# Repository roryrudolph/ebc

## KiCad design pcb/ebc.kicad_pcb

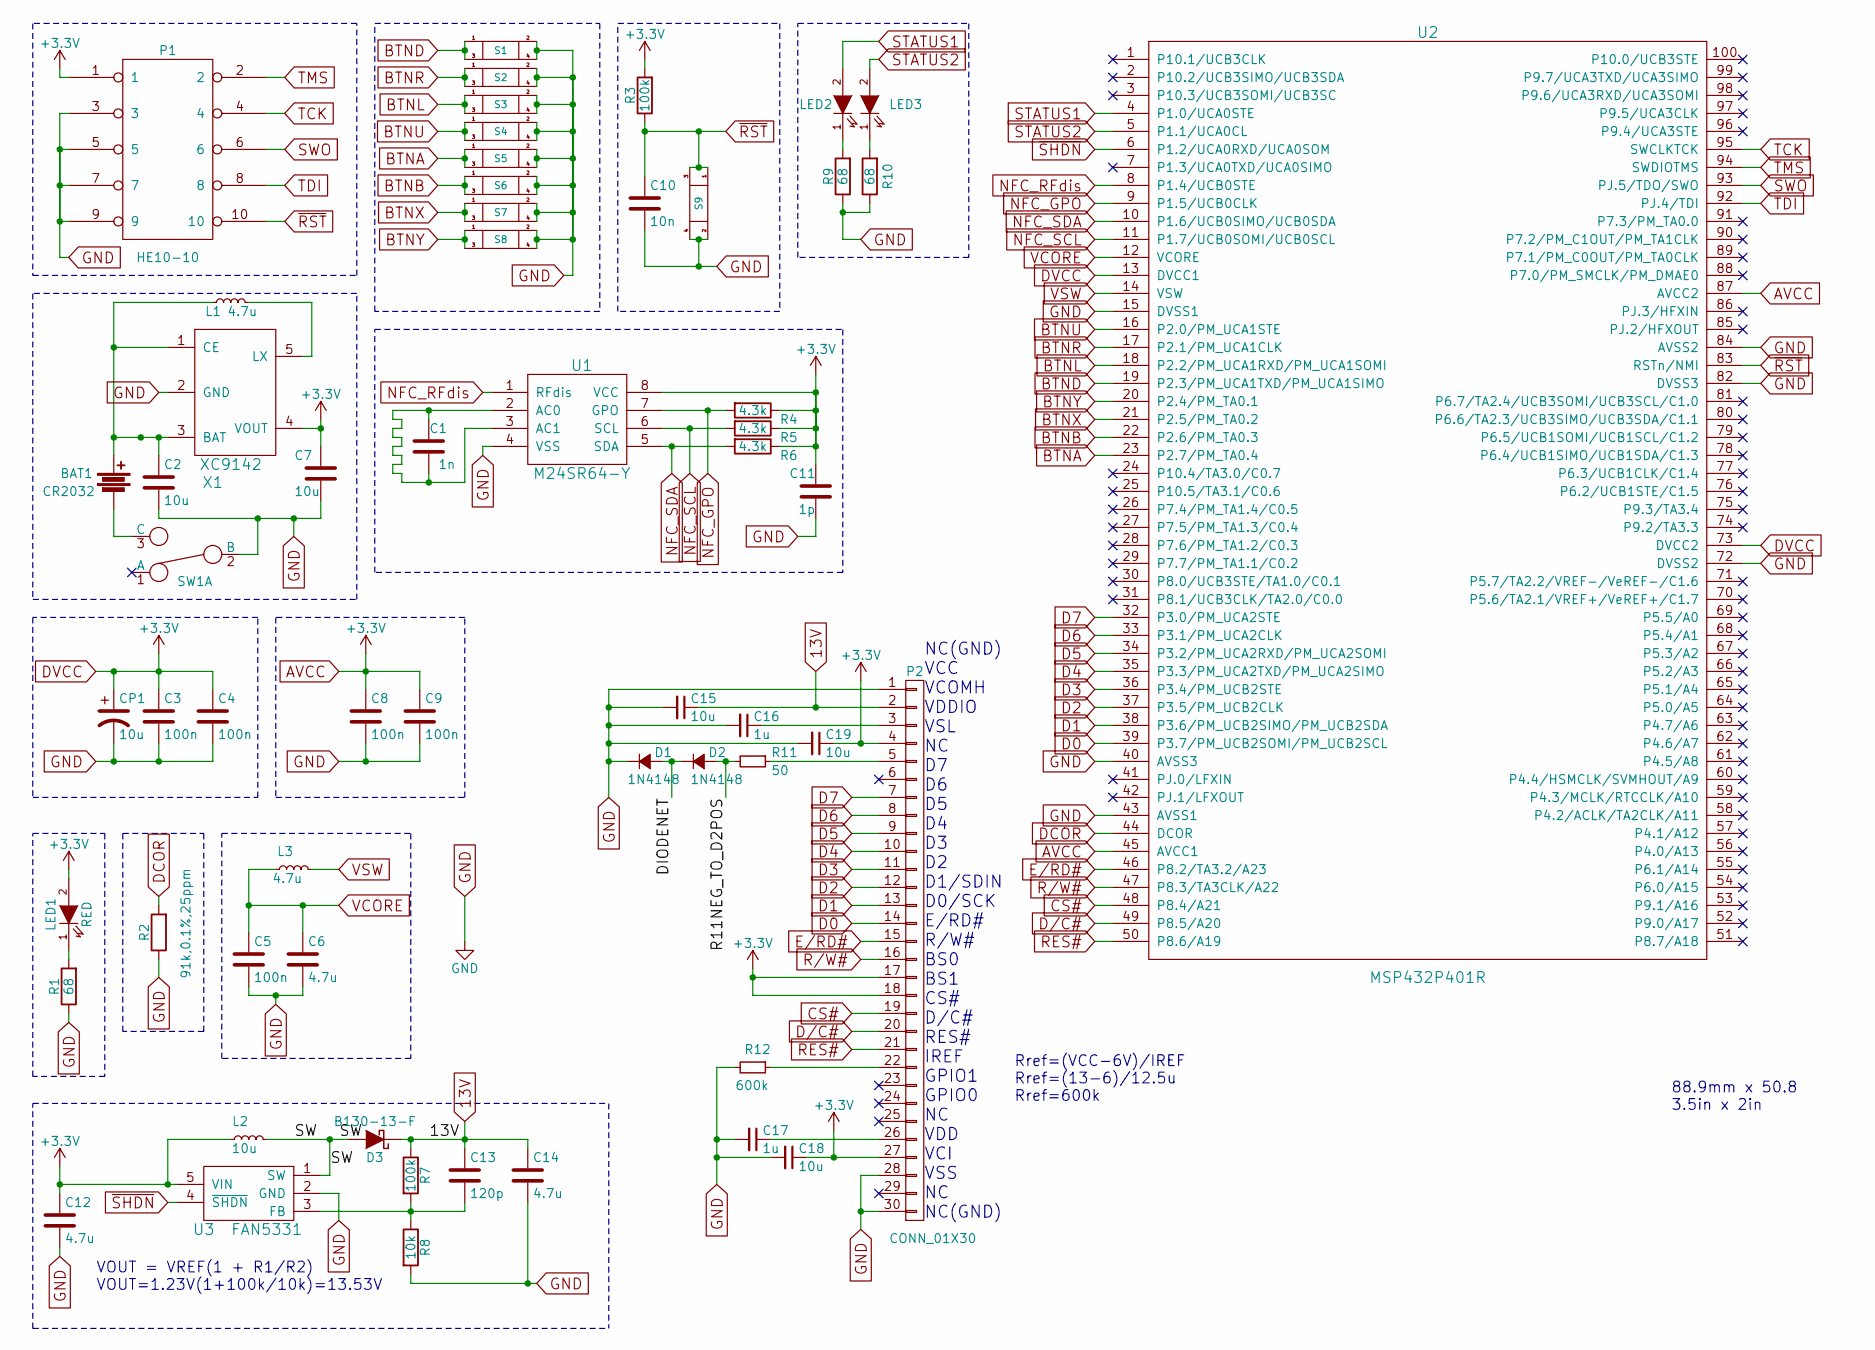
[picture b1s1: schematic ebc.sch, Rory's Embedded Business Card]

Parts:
BAT1: CR2032; BK-912-G-TR
C1: 1n; 0805
C2, C7, C15, C18, C19: 10u; 0805
C3, C4, C5, C8, C9: 100n; 0805
C6, C12, C14: 4.7u; 0805
C10: 10n; 0805
C11: 1p; 0805
C13: 120p; 0805
C16, C17: 1u; 0805
CP1: 10u; 1206
D1, D2: 1N4148; SOD-323
D3: B130-13-F; DO-214AC
L1, L3: 4.7u; 1210
L2: 10u; 1210
LED1, LED2, LED3: RED; 1206
P1: HE10-10; 2x5_PIN_THROUGHHOLE
P2: CONN_01X30; XF2M-3015-1A
R1, R9, R10: 68; 0805
R2: 91k,0.1%,25ppm; 0805
R3, R7: 100k; 0805
R4, R5, R6: 4.3k; 0805
R8: 10k; 0805
R11: 50; 0805
R12: 600k; 0805
S1, S2, S3, S4, S5, S6, S7, S8, S9: 222AMVBAR
SW1: Switch_SPDT_x2; PCM12SMTR
U1: M24SR64-Y
U2: MSP432P401R
U3: FAN5331
X1: XC9142

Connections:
13V: C13.1, C14.1, C15.1, D3.1 (K), P2.2, R7.1
/DIODENET: D1.2 (A), D2.1 (K)
/R11NEG_TO_D2POS: D2.2 (A), R11.2
/SW: D3.2 (A), L2.2, U3.1 (SW)
AVCC: C3.1, C4.1, C7.1, C8.1, C9.1, C11.1, C12.1, C18.1, C19.1, CP1.1, L2.1, LED1.2 (A), P1.1, P2.4, P2.17, P2.18, P2.27, R3.2, R4.1, R5.1, R6.1, U1.8 (VCC), U2.13 (DVCC1), U2.45 (AVCC1), U2.73 (DVCC2), U2.87 (AVCC2), U3.5 (VIN), X1.4 (VOUT)
BTNA: S5.1, S5.3, U2.23 (P2.7/PM_TA0.4)
BTNB: S6.1, S6.3, U2.22 (P2.6/PM_TA0.3)
BTND: S1.1, S1.3, U2.19 (P2.3/PM_UCA1TXD/PM_UCA1SIMO)
BTNL: S3.1, S3.3, U2.18 (P2.2/PM_UCA1RXD/PM_UCA1SOMI)
BTNR: S2.1, S2.3, U2.17 (P2.1/PM_UCA1CLK)
BTNU: S4.1, S4.3, U2.16 (P2.0/PM_UCA1STE)
BTNX: S7.1, S7.3, U2.21 (P2.5/PM_TA0.2)
BTNY: S8.1, S8.3, U2.20 (P2.4/PM_TA0.1)
CS#: P2.19, U2.48 (P8.4/A21)
D0: P2.14, U2.39 (P3.7/PM_UCB2SOMI/PM_UCB2SCL)
D1: P2.13, U2.38 (P3.6/PM_UCB2SIMO/PM_UCB2SDA)
D2: P2.12, U2.37 (P3.5/PM_UCB2CLK)
D3: P2.11, U2.36 (P3.4/PM_UCB2STE)
D4: P2.10, U2.35 (P3.3/PM_UCA2TXD/PM_UCA2SIMO)
D5: P2.9, U2.34 (P3.2/PM_UCA2RXD/PM_UCA2SOMI)
D6: P2.8, U2.33 (P3.1/PM_UCA2CLK)
D7: P2.7, U2.32 (P3.0/PM_UCA2STE)
D/C#: P2.20, U2.49 (P8.5/A20)
DCOR: R2.2, U2.44 (DCOR)
E/RD#: P2.15, U2.46 (P8.2/TA3.2/A23)
GND: C2.2, C3.2, C4.2, C5.2, C6.2, C7.2, C8.2, C9.2, C10.2, C11.2, C12.2, C14.2, C15.2, C16.2, C17.2, C18.2, C19.2, CP1.2, D1.1 (K), P1.3, P1.5, P1.7, P1.9, P2.1, P2.28, P2.30, R1.1, R2.1, R8.2, R9.1, R10.1, R12.2, S1.2, S1.4, S2.2, S2.4, S3.2, S3.4, S4.2, S4.4, S5.2, S5.4, S6.2, S6.4, S7.2, S7.4, S8.2, S8.4, S9.2, S9.4, SW1.2 (B), U1.4 (VSS), U2.15 (DVSS1), U2.40 (AVSS3), U2.43 (AVSS1), U2.72 (DVSS2), U2.82 (DVSS3), U2.84 (AVSS2), U3.2 (GND), X1.2 (GND)
NFC_GPO: R4.2, U1.7 (GPO), U2.9 (P1.5/UCB0CLK)
NFC_RFdis: U1.1 (RFdis), U2.8 (P1.4/UCB0STE)
NFC_SCL: R5.2, U1.6 (SCL), U2.11 (P1.7/UCB0SOMI/UCB0SCL)
NFC_SDA: R6.2, U1.5 (SDA), U2.10 (P1.6/UCB0SIMO/UCB0SDA)
unnamed: BAT1.1, C2.1, L1.1, X1.1 (CE), X1.3 (BAT)
unnamed: BAT1.2, SW1.3 (C)
unnamed: C1.1, C1.2, U1.2 (AC0), U1.3 (AC1)
unnamed: C13.2, R7.2, R8.1, U3.3 (FB)
unnamed: C16.1, P2.3
unnamed: C17.1, P2.26
unnamed: L1.2, X1.5 (LX)
unnamed: LED1.1 (K), R1.2
unnamed: LED2.1 (K), R9.2
unnamed: LED3.1 (K), R10.2
unnamed: P2.5, R11.1
unnamed: P2.22, R12.1
R/W#: P2.16, U2.47 (P8.3/TA3CLK/A22)
RES#: P2.21, U2.50 (P8.6/A19)
STATUS1: LED2.2 (A), U2.4 (P1.0/UCA0STE)
STATUS2: LED3.2 (A), U2.5 (P1.1/UCA0CL)
SWO: P1.6, U2.93 (PJ.5/TDO/SWO)
TCK: P1.4, U2.95 (SWCLKTCK)
TDI: P1.8, U2.92 (PJ.4/TDI)
TMS: P1.2, U2.94 (SWDIOTMS)
VCORE: C5.1, C6.1, L3.1, U2.12 (VCORE)
VSW: L3.2, U2.14 (VSW)
~RST: C10.1, P1.10, R3.1, S9.1, S9.3, U2.83 (RSTn/NMI)
~SHDN: U2.6 (P1.2/UCA0RXD/UCA0SOM), U3.4 (~SHDN)

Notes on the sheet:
VOUT = VREF(1 + R1/R2) VOUT=1.23V(1+100k/10k)=13.53V
88.9mm x 50.8 3.5in x 2in
NC(GND) VCC VCOMH VDDIO VSL NC D7 D6 D5 D4 D3 D2 D1/SDIN D0/SCK E/RD# R/W# BS0 BS1 CS# D/C# RES# IREF GPIO1 GPIO0 NC VDD VCI VSS NC NC(GND)
Rref=(VCC-6V)/IREF Rref=(13-6)/12.5u Rref=600k

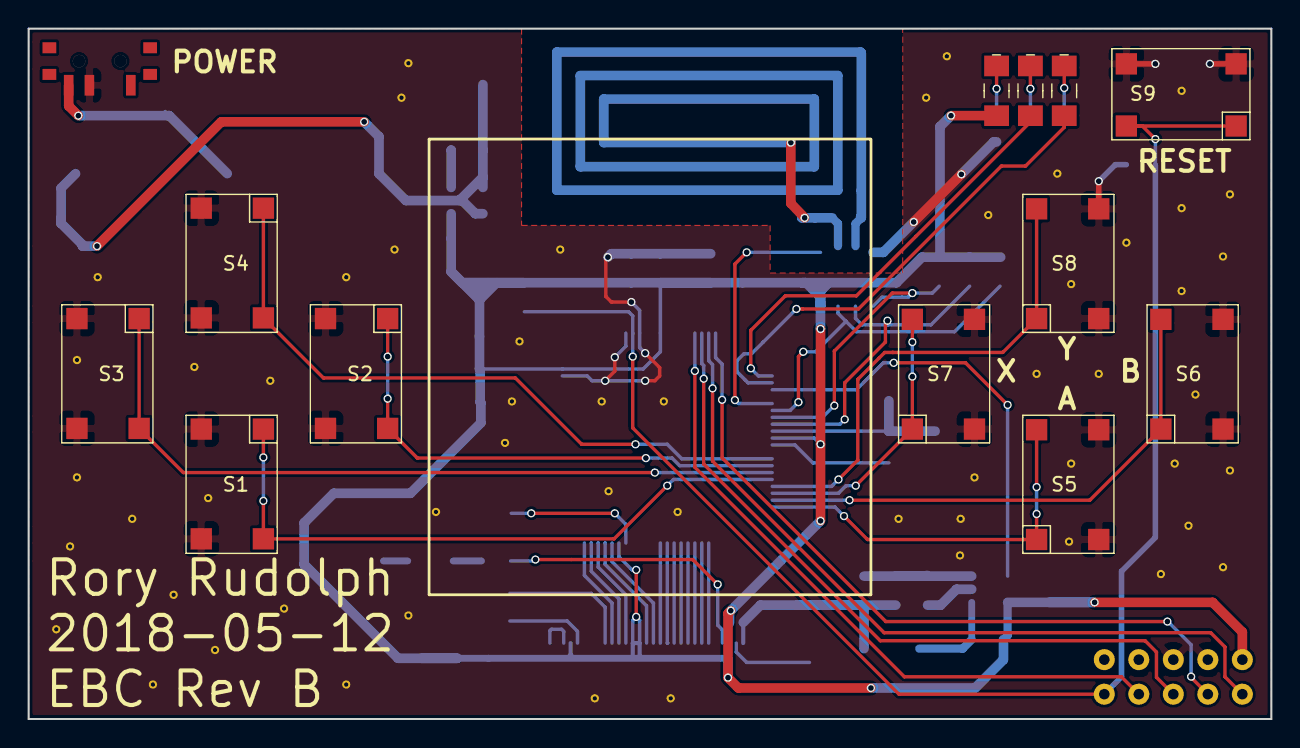
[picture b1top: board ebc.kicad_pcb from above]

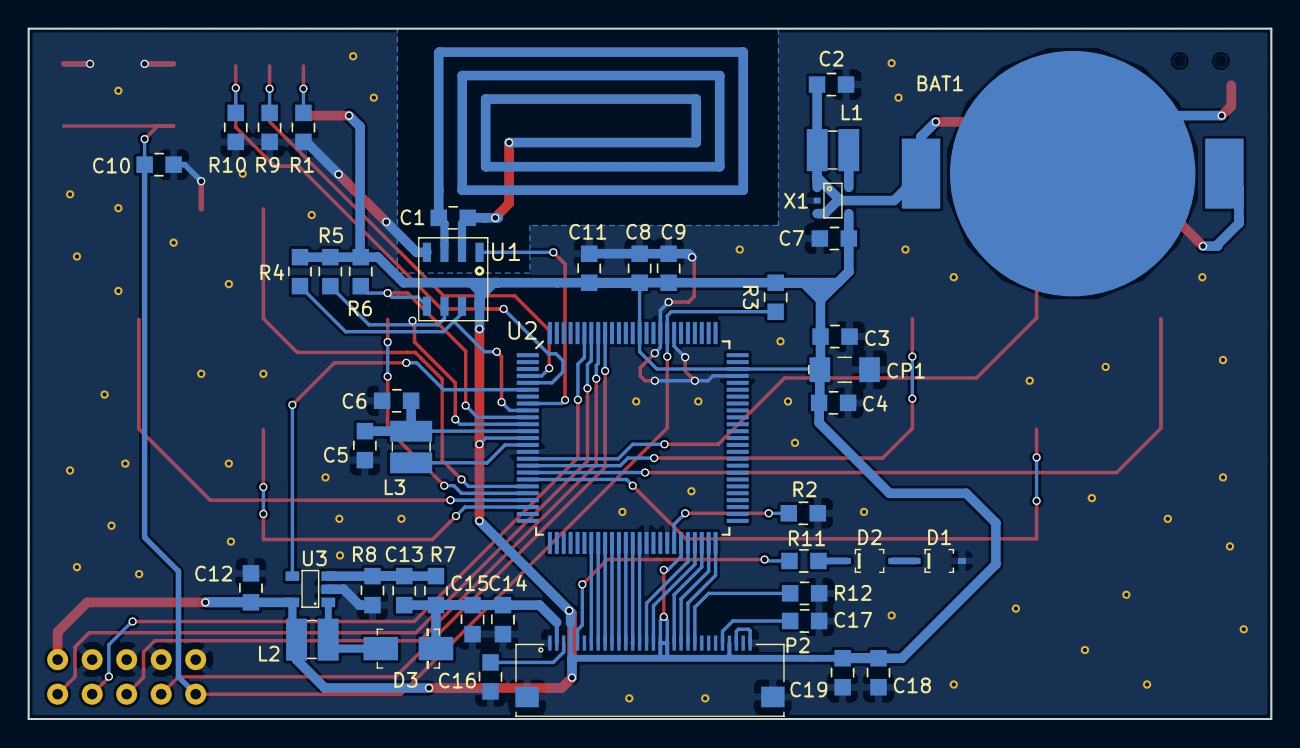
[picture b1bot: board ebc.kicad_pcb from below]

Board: 2 copper layers, 90.0 x 50.0 mm, 58 parts (44 on the bottom side), 54 nets.

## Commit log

2018-05-08 - initial commit for ebc rev B
2018-05-08 - organized the project directory for code and pcb
2018-05-09 - schematic almost finished. just trying to pass electrical check
2018-05-09 - netlist generated, component selection begun
2018-05-09 - added gitignore
2018-05-12 - layout about 40% done
2018-05-12 - pcb finished! - unignored gitignore files
2018-05-13 - pcb gerbered out and stencils created
2018-05-13 - began code
2018-05-14 - BROKEN! Temporary commit while changing computers - added startup and system MSP files
2018-05-14 - added OSH Park top and bottom PCB images
2018-06-01 - code started
